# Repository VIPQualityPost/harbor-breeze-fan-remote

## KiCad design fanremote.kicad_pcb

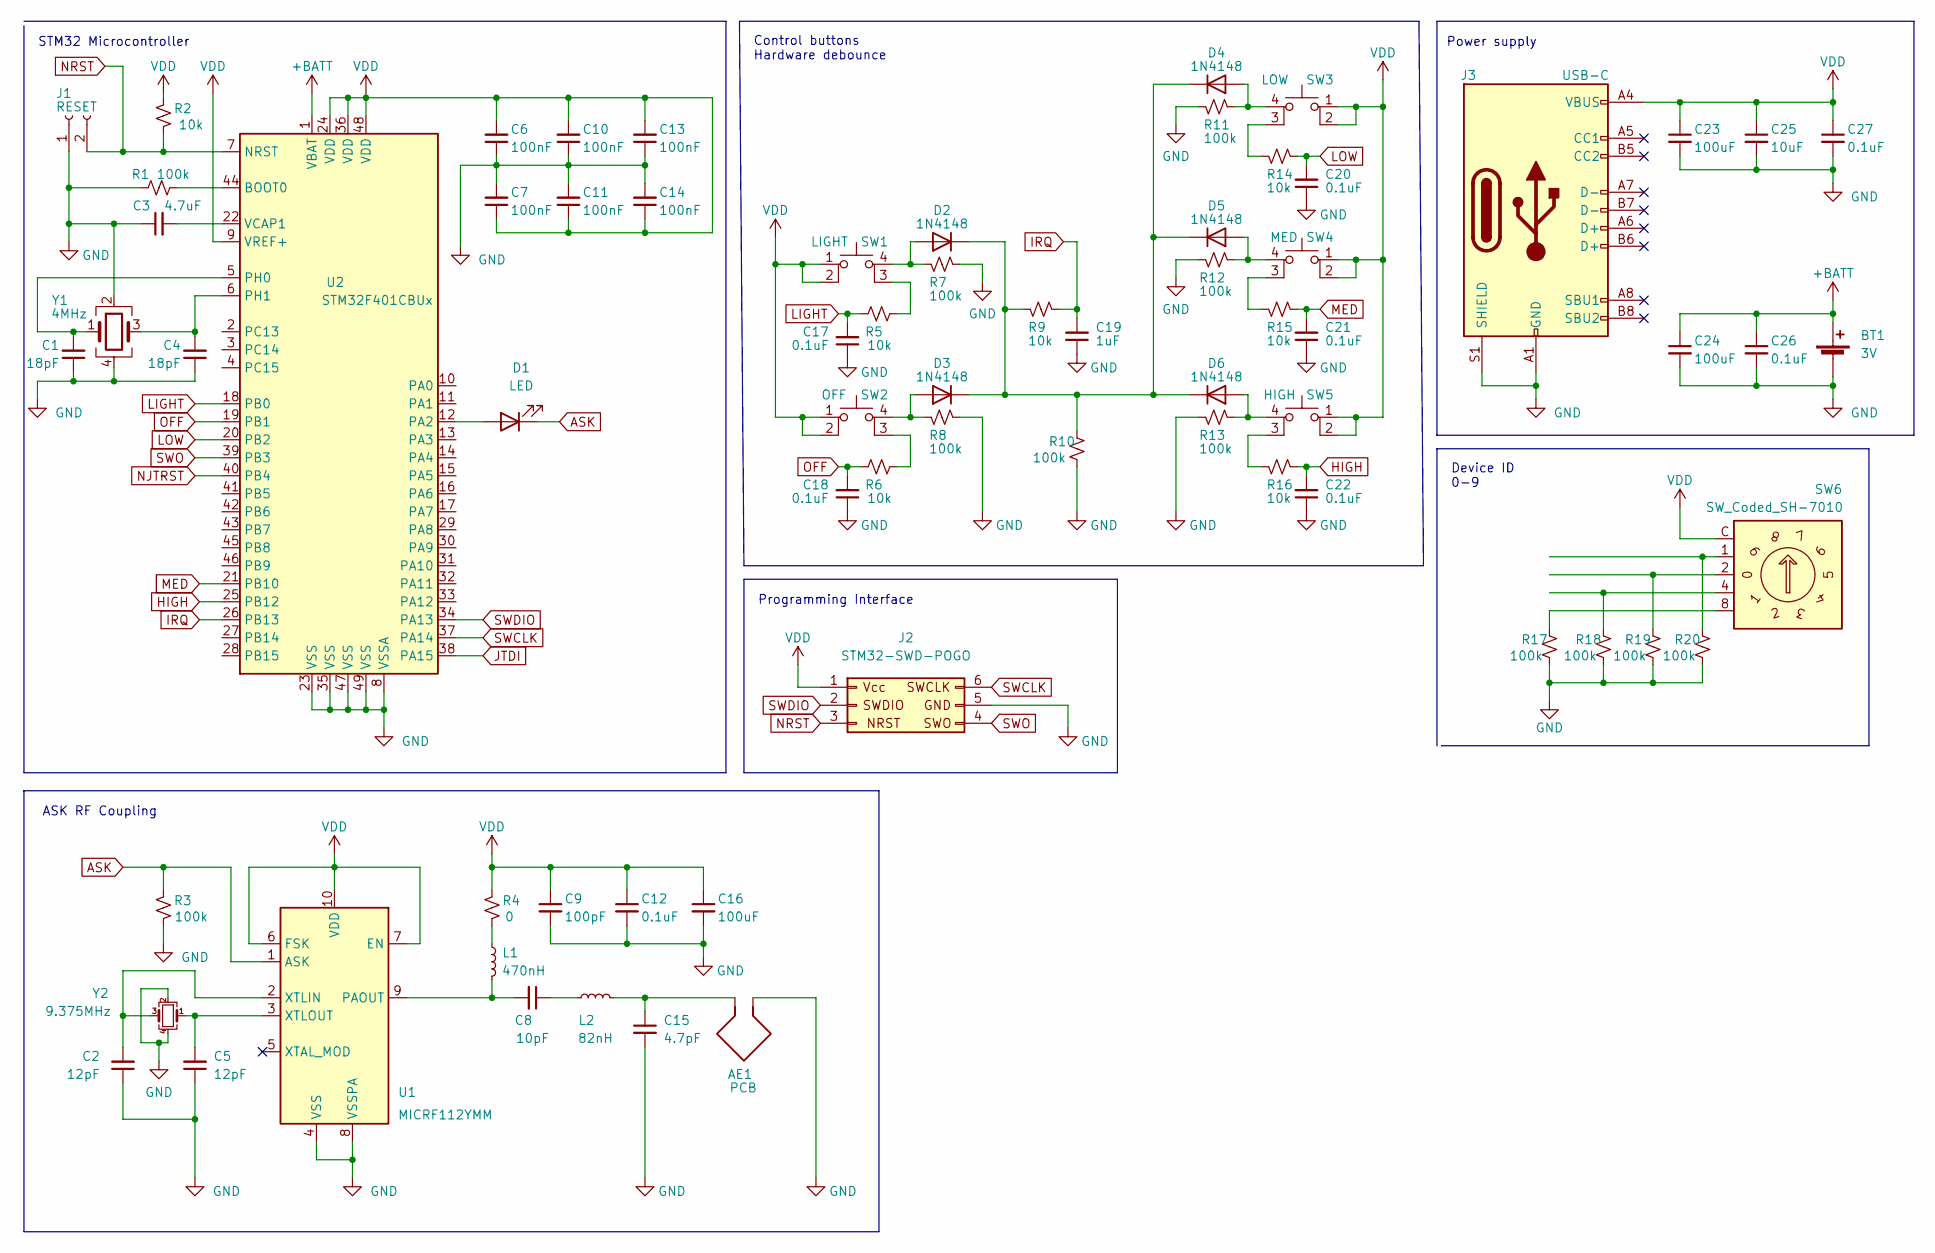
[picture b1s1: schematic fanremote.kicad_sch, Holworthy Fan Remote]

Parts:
AE1: PCB; antenna-300-500MHz
BT1: 3V; BatteryHolder_MPD_BC2003_1x2032
C1, C4: 18pF; C_0603_1608Metric
C2, C5: 12pF; C_0603_1608Metric
C3: 4.7uF; C_0603_1608Metric
C6, C7, C10, C11, C13, C14: 100nF; C_0603_1608Metric
C8: 10pF; C_0603_1608Metric
C9: 100pF; C_0603_1608Metric
C12, C17, C18, C20, C21, C22, C26, C27: 0.1uF; C_0603_1608Metric
C15: 4.7pF; C_0603_1608Metric
C16, C23, C24: 100uF; C_0603_1608Metric
C19: 1uF; C_0603_1608Metric
C25: 10uF; C_0603_1608Metric
D1: LED; D_0603_1608Metric
D2, D3, D4, D5, D6: 1N4148; D_0603_1608Metric
J1: RESET; SolderJumper-2_P1.3mm_Open_RoundedPad1.0x1.5mm
J2: STM32-SWD-POGO; SWD_pogo_landing
J3: USB-C; USB_C_Receptacle_HRO_TYPE-C-31-M-12
L1: 470nH; L_0603_1608Metric
L2: 82nH; L_0603_1608Metric
R1, R3, R7, R8, R10, R11, R12, R13, R17, R18, R19, R20: 100k; R_0603_1608Metric
R2, R5, R6, R9, R14, R15, R16: 10k; R_0603_1608Metric
R4: 0; R_0603_1608Metric
SW1: LIGHT; PTS526 SKG15 SMTR2 LFS
SW2: OFF; PTS526 SKG15 SMTR2 LFS
SW3: LOW; PTS526 SKG15 SMTR2 LFS
SW4: MED; PTS526 SKG15 SMTR2 LFS
SW5: HIGH; PTS526 SKG15 SMTR2 LFS
SW6: SW_Coded_SH-7010; Nidec_Copal_SH-7010A
U1: MICRF112YMM; MSOP-10_3x3mm_P0.5mm
U2: STM32F401CBUx; QFN-48-1EP_7x7mm_P0.5mm_EP5.6x5.6mm
Y1: 4MHz; Crystal_SMD_Abracon_ABS25-4Pin_8.0x3.8mm
Y2: 9.375MHz; Crystal_SMD_Abracon_ABS25-4Pin_8.0x3.8mm

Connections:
+BATT: BT1.1 (+), C24.1, C26.1, U2.1 (VBAT)
ASK: D1.1 (K), R3.1, U1.1 (ASK)
GND: AE1.2, BT1.2 (-), C1.1, C2.1, C3.1, C4.1, C5.1, C6.1, C7.2, C9.2, C10.1, C11.2, C12.2, C13.1, C14.2, C15.2, C16.2, C17.1, C18.1, C19.1, C20.1, C21.1, C22.1, C23.2, C24.2, C25.2, C26.2, C27.2, J1.1, J2.5, J3.A1 (GND), J3.A12 (GND), J3.B1 (GND), J3.B12 (GND), J3.S1 (SHIELD), R1.1, R3.2, R7.1, R8.1, R10.2, R11.2, R12.2, R13.2, R17.2, R18.2, R19.2, R20.2, U1.4 (VSS), U1.8 (VSSPA), U2.8 (VSSA), U2.23 (VSS), U2.35 (VSS), U2.47 (VSS), U2.49 (VSS), Y1.2, Y1.4, Y2.2, Y2.4
HIGH: C22.2, R16.1, U2.25 (PB12)
IRQ: C19.2, R9.1, U2.26 (PB13)
JTDI: U2.38 (PA15)
LIGHT: C17.2, R5.1, U2.18 (PB0)
LOW: C20.2, R14.1, U2.20 (PB2)
MED: C21.2, R15.1, U2.21 (PB10)
NJTRST: U2.40 (PB4)
NRST: J1.2, J2.3, R2.2, U2.7 (NRST)
unnamed: C1.2, U2.5 (PH0), Y1.1
unnamed: C2.2, U1.2 (XTLIN), Y2.3
unnamed: C3.2, U2.22 (VCAP1)
unnamed: C4.2, U2.6 (PH1), Y1.3
unnamed: C5.2, U1.3 (XTLOUT), Y2.1
unnamed: C8.1, L2.2
unnamed: C8.2, L1.1, U1.9 (PAOUT)
unnamed: AE1.1, C15.1, L2.1
unnamed: D1.2 (A), U2.12 (PA2)
unnamed: D2.1 (K), D3.1 (K), D4.1 (K), D5.1 (K), D6.1 (K), R9.2, R10.1
unnamed: D2.2 (A), R7.2, SW1.4 (A)
unnamed: D3.2 (A), R8.2, SW2.4 (A)
unnamed: D4.2 (A), R11.1, SW3.4 (A)
unnamed: D5.2 (A), R12.1, SW4.4 (A)
unnamed: D6.2 (A), R13.1, SW5.4 (A)
unnamed: L1.2, R4.2
unnamed: R1.2, U2.44 (BOOT0)
unnamed: R5.2, SW1.3 (K)
unnamed: R6.2, SW2.3 (K)
unnamed: R14.2, SW3.3 (K)
unnamed: R15.2, SW4.3 (K)
unnamed: R16.2, SW5.3 (K)
unnamed: R17.1, SW6.8
unnamed: R18.1, SW6.4
unnamed: R19.1, SW6.2
unnamed: R20.1, SW6.1
OFF: C18.2, R6.1, U2.19 (PB1)
SWCLK: J2.6, U2.37 (PA14)
SWDIO: J2.2, U2.34 (PA13)
SWO: J2.4, U2.39 (PB3)
VDD: C6.2, C7.1, C9.1, C10.2, C11.1, C12.1, C13.2, C14.1, C16.1, C23.1, C25.1, C27.1, J2.1, J3.A4 (VBUS), J3.A9 (VBUS), J3.B4 (VBUS), J3.B9 (VBUS), R2.1, R4.1, SW1.1, SW1.2, SW2.1, SW2.2, SW3.1, SW3.2, SW4.1, SW4.2, SW5.1, SW5.2, SW6.C, U1.6 (FSK), U1.7 (EN), U1.10 (VDD), U2.9 (VREF+), U2.24 (VDD), U2.36 (VDD), U2.48 (VDD)

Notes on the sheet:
Device ID 0-9
Power supply
STM32 Microcontroller
ASK RF Coupling
Programming Interface
Control buttons Hardware debounce

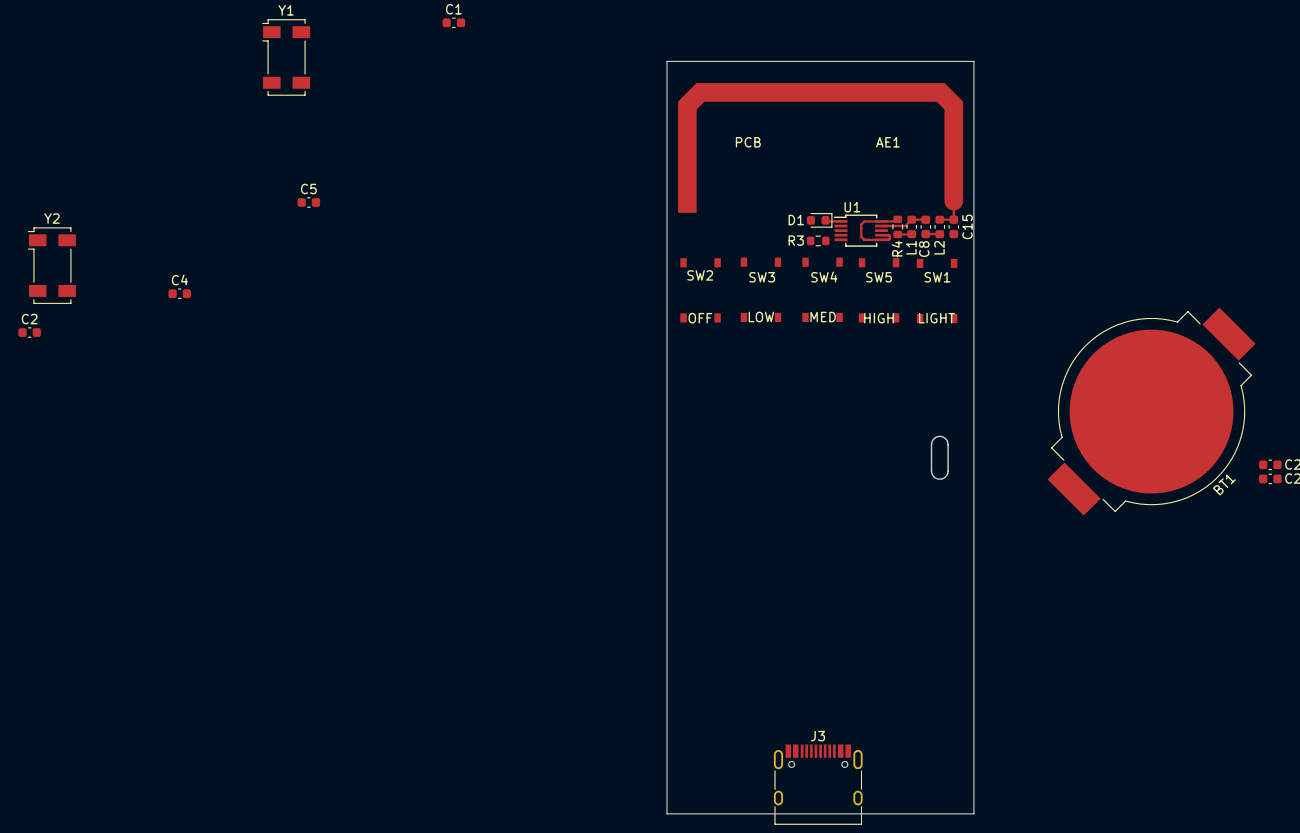
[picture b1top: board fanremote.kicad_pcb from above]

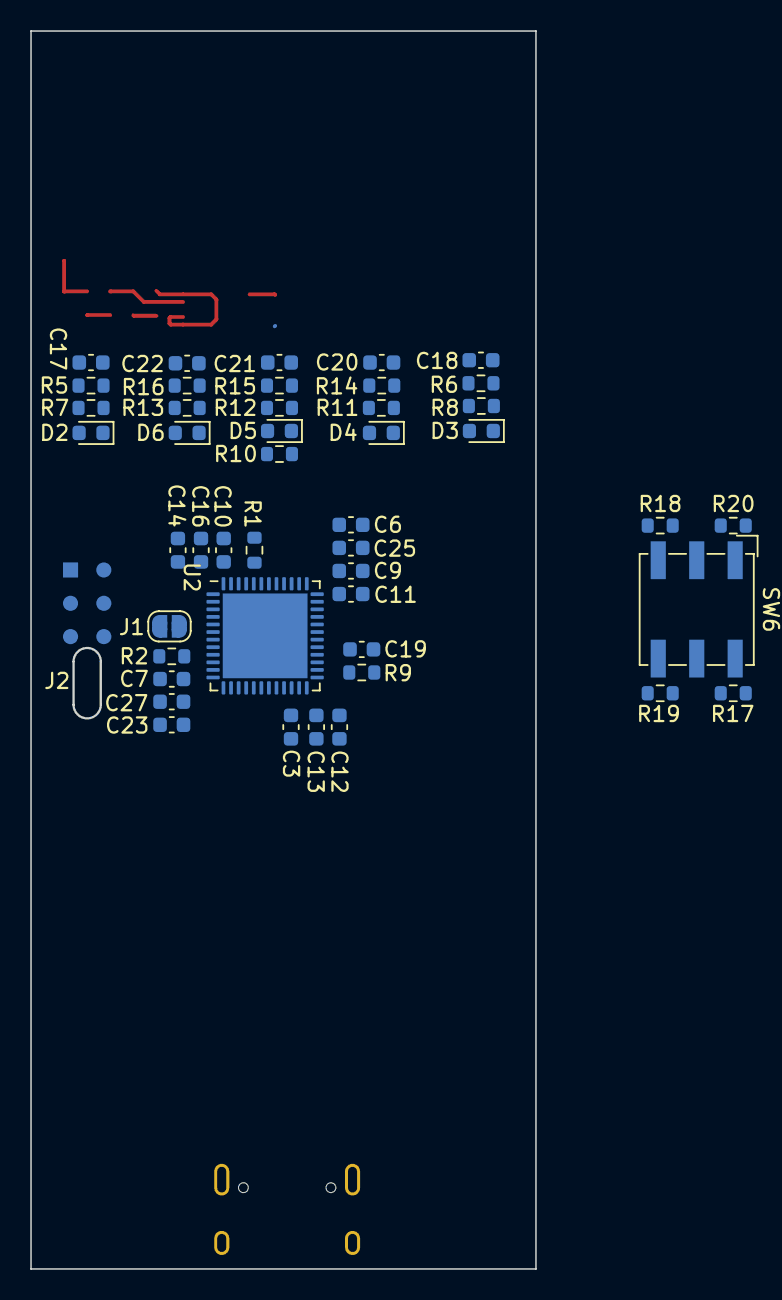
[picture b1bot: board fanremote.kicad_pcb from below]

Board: 2 copper layers, 33.4 x 81.8 mm, 70 parts (46 on the bottom side), 40 nets.

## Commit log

2022-11-18 added files
2023-02-13 Auto-commit Mon Feb 13 12:20:11 EST 2023
2023-02-17 Auto-commit Thu Feb 16 21:35:00 EST 2023
2023-02-17 Auto-commit Fri Feb 17 12:27:49 EST 2023
2023-02-17 Auto-commit Fri Feb 17 13:04:06 EST 2023
2023-02-17 Remove ignored files
